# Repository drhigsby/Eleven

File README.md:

Eleven is an 11u wide traditionally staggered keyboard with multiple spacebar arrangements. 

* Keyboard Maintainer: [H. Bond](https://github.com/drhigsby)
* Hardware Supported: Warpstone (https://github.com/drhigsby/eleven)
* Hardware Availability: make your own/check repo files

Make example for this keyboard (after setting up your build environment):

    make eleven:default

See the [build environment setup](https://docs.qmk.fm/#/getting_started_build_tools) and the [make instructions](https://docs.qmk.fm/#/getting_started_make_guide) for more information. Brand new to QMK? Start with our [Complete Newbs Guide](https://docs.qmk.fm/#/newbs).

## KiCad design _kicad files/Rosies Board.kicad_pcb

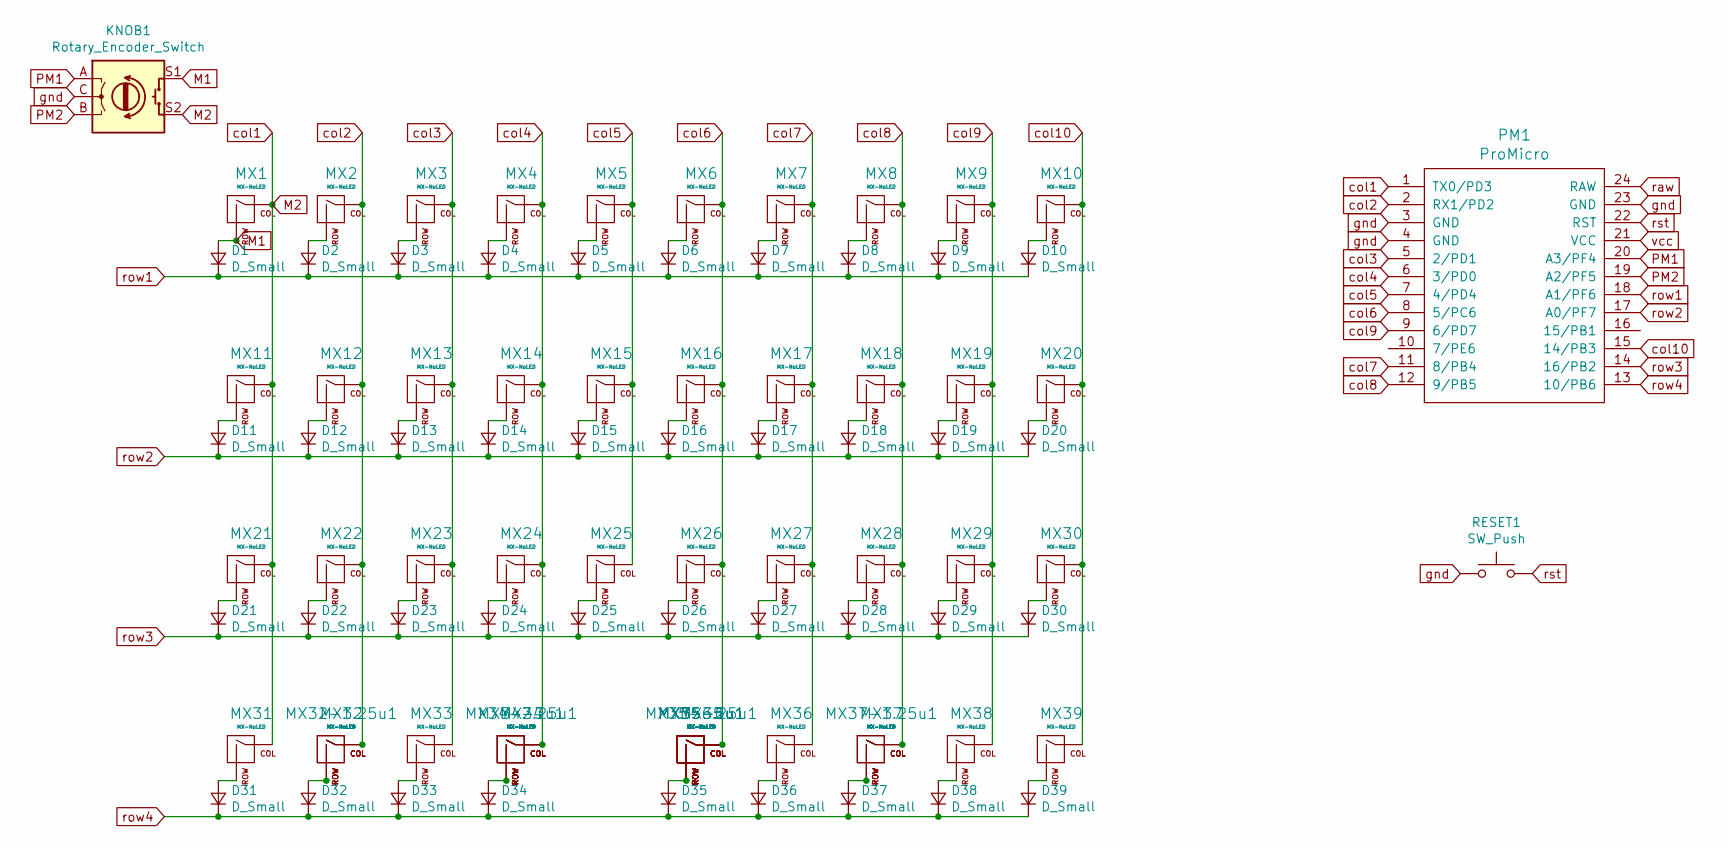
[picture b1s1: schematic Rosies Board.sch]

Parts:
D1, D2, D3, D4, D5, D6, D7, D8, D9, D10, D11, D12, D13, D14, D15, D16, D17, D18, D19, D20, D21, D22, D23, D24, D25, D26, D27, D28, D29, D30, D31, D32, D33, D34, D35, D36, D37, D38, D39: D_Small; Diode-Hybrid-Back
KNOB1: Rotary_Encoder_Switch; RotaryEncoder_Alps_EC11E-Switch_Vertical_H20mm_CircularMoun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
MX1, MX2, MX3, MX4, MX5, MX6, MX7, MX8, MX9, MX10, MX12, MX13, MX14, MX15, MX16, MX17, MX18, MX19, MX22, MX23, MX24, MX25, MX26, MX27, MX28, MX29, MX32, MX33, MX37, MX39: MX-NoLED; MXOnly-1U-NoLED
MX11, MX30, MX31, MX32-1.25u1, MX36, MX37-1.25u1, MX38: MX-NoLED; MXOnly-1.25U-NoLED
MX20, MX21: MX-NoLED; MXOnly-1.75U-NoLED
MX34, MX35-2u1: MX-NoLED; MXOnly-2U-ReversedStabilizers-NoLED
MX34-2.25u1, MX35: MX-NoLED; MXOnly-2.25U-ReversedStabilizers-NoLED
MX34-3u1, MX35-3u1: MX-NoLED; MXOnly-3U-ReversedStabilizers-NoLED
MX35-6.25u1: MX-NoLED; MXOnly-6.25U-ReversedStabilizers-NoLED
MX35-6u1: MX-NoLED; MXOnly-6U-Centered-ReversedStabilizers-NoLED
PM1: ProMicro; ArduinoProMicro
RESET1: SW_Push; SKQG-1155865

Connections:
M1: D1.2 (A), KNOB1.S1, MX1.2 (ROW)
M2: KNOB1.S2, MX1.1 (COL), MX11.1 (COL), MX21.1 (COL), MX31.1 (COL), PM1.1 (TX0/PD3)
unnamed: D2.2 (A), MX2.2 (ROW)
unnamed: D3.2 (A), MX3.2 (ROW)
unnamed: D4.2 (A), MX4.2 (ROW)
unnamed: D5.2 (A), MX5.2 (ROW)
unnamed: D6.2 (A), MX6.2 (ROW)
unnamed: D7.2 (A), MX7.2 (ROW)
unnamed: D8.2 (A), MX8.2 (ROW)
unnamed: D9.2 (A), MX9.2 (ROW)
unnamed: D10.2 (A), MX10.2 (ROW)
unnamed: D11.2 (A), MX11.2 (ROW)
unnamed: D12.2 (A), MX12.2 (ROW)
unnamed: D13.2 (A), MX13.2 (ROW)
unnamed: D14.2 (A), MX14.2 (ROW)
unnamed: D15.2 (A), MX15.2 (ROW)
unnamed: D16.2 (A), MX16.2 (ROW)
unnamed: D17.2 (A), MX17.2 (ROW)
unnamed: D18.2 (A), MX18.2 (ROW)
unnamed: D19.2 (A), MX19.2 (ROW)
unnamed: D20.2 (A), MX20.2 (ROW)
unnamed: D21.2 (A), MX21.2 (ROW)
unnamed: D22.2 (A), MX22.2 (ROW)
unnamed: D23.2 (A), MX23.2 (ROW)
unnamed: D24.2 (A), MX24.2 (ROW)
unnamed: D25.2 (A), MX25.2 (ROW)
unnamed: D26.2 (A), MX26.2 (ROW)
unnamed: D27.2 (A), MX27.2 (ROW)
unnamed: D28.2 (A), MX28.2 (ROW)
unnamed: D29.2 (A), MX29.2 (ROW)
unnamed: D30.2 (A), MX30.2 (ROW)
unnamed: D31.2 (A), MX31.2 (ROW)
unnamed: D32.2 (A), MX32.2 (ROW), MX32-1.25u1.2 (ROW)
unnamed: D33.2 (A), MX33.2 (ROW)
unnamed: D34.2 (A), MX34.2 (ROW), MX34-2.25u1.2 (ROW), MX34-3u1.2 (ROW)
unnamed: D35.2 (A), MX35.2 (ROW), MX35-2u1.2 (ROW), MX35-3u1.2 (ROW), MX35-6.25u1.2 (ROW), MX35-6u1.2 (ROW)
unnamed: D36.2 (A), MX36.2 (ROW)
unnamed: D37.2 (A), MX37.2 (ROW), MX37-1.25u1.2 (ROW)
unnamed: D38.2 (A), MX38.2 (ROW)
unnamed: D39.2 (A), MX39.2 (ROW)
PM1: KNOB1.A, PM1.20 (A3/PF4)
PM2: KNOB1.B, PM1.19 (A2/PF5)
col2: MX2.1 (COL), MX12.1 (COL), MX22.1 (COL), MX32.1 (COL), MX32-1.25u1.1 (COL), PM1.2 (RX1/PD2)
col3: MX3.1 (COL), MX13.1 (COL), MX23.1 (COL), MX33.1 (COL), PM1.5 (2/PD1)
col4: MX4.1 (COL), MX14.1 (COL), MX24.1 (COL), MX34.1 (COL), MX34-2.25u1.1 (COL), MX34-3u1.1 (COL), PM1.6 (3/PD0)
col5: MX5.1 (COL), MX15.1 (COL), MX25.1 (COL), PM1.7 (4/PD4)
col6: MX6.1 (COL), MX16.1 (COL), MX26.1 (COL), MX35.1 (COL), MX35-2u1.1 (COL), MX35-3u1.1 (COL), MX35-6.25u1.1 (COL), MX35-6u1.1 (COL), PM1.8 (5/PC6)
col7: MX7.1 (COL), MX17.1 (COL), MX27.1 (COL), MX36.1 (COL), PM1.11 (8/PB4)
col8: MX8.1 (COL), MX18.1 (COL), MX28.1 (COL), MX37.1 (COL), MX37-1.25u1.1 (COL), PM1.12 (9/PB5)
col9: MX9.1 (COL), MX19.1 (COL), MX29.1 (COL), MX38.1 (COL), PM1.9 (6/PD7)
col10: MX10.1 (COL), MX20.1 (COL), MX30.1 (COL), MX39.1 (COL), PM1.15 (14/PB3)
gnd: KNOB1.C, PM1.3 (GND), PM1.4 (GND), PM1.23 (GND), RESET1.1
raw: PM1.24 (RAW)
row1: D1.1 (K), D2.1 (K), D3.1 (K), D4.1 (K), D5.1 (K), D6.1 (K), D7.1 (K), D8.1 (K), D9.1 (K), D10.1 (K), PM1.18 (A1/PF6)
row2: D11.1 (K), D12.1 (K), D13.1 (K), D14.1 (K), D15.1 (K), D16.1 (K), D17.1 (K), D18.1 (K), D19.1 (K), D20.1 (K), PM1.17 (A0/PF7)
row3: D21.1 (K), D22.1 (K), D23.1 (K), D24.1 (K), D25.1 (K), D26.1 (K), D27.1 (K), D28.1 (K), D29.1 (K), D30.1 (K), PM1.14 (16/PB2)
row4: D31.1 (K), D32.1 (K), D33.1 (K), D34.1 (K), D35.1 (K), D36.1 (K), D37.1 (K), D38.1 (K), D39.1 (K), PM1.13 (10/PB6)
rst: PM1.22 (RST), RESET1.2
vcc: PM1.21 (VCC)

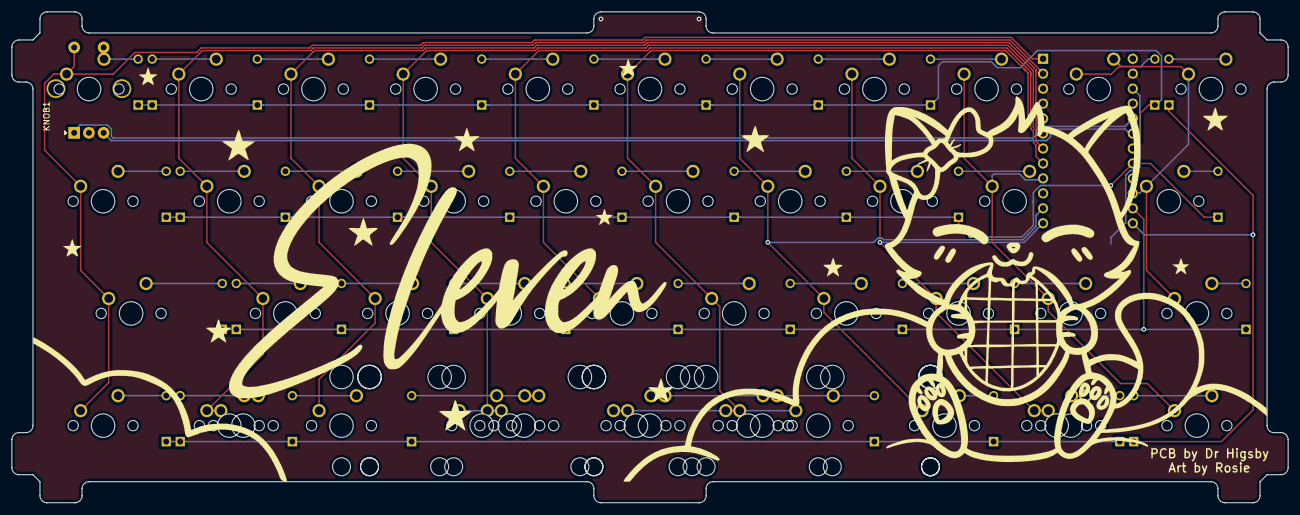
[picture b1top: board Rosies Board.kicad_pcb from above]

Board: 2 copper layers, 216.7 x 83.3 mm, 89 parts (1 on the bottom side), 57 nets.

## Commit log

2021-02-23 update silks
2021-02-23 moving files around
2021-06-15 eleven with tabs update
2021-06-15 added qmk stuff
2021-06-15 qmk stuff
2021-06-15 repo cleanup
2021-06-15 further cleanup
2021-06-15 removing useless subfolder
2021-06-15 removed zip
2021-06-15 added to required hardware list
2021-06-21 adding zmk firmware as a zip
2021-09-20 updating kicad related things
2021-09-20 added PM cover/feet & updated case readme
2021-09-20 updated case readme
